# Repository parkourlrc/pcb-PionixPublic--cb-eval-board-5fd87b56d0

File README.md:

# ChargeBridge Evaluation Board

This repository contains the KiCad project files for the **ChargeBridge Evaluation Board**, released as open hardware.

> [!NOTE]  
> KiCad version **9.0.3 or newer** is required to open this project. [Download KiCad](https://www.kicad.org/)

### Overview

This evaluation board is designed to facilitate testing and development with **Pionix ChargeBridge modules**, supporting **all major charging standards**. It is compatible with both **EVSE (Electric Vehicle Supply Equipment)** and **EV (Electric Vehicle)** ChargeBridge modules.

### Use Cases

* **Dual-Board Evaluation Setup**:
  Using two evaluation boards (one with an EVSE module and one with an EV module), you can create a fully functional desktop test environment where the EV module simulates a vehicle being charged by the EVSE module.

* **Standalone Charger Development**:
  A single board can be integrated into a **fully operational AC or DC charger** by connecting appropriate external components such as:

  * Contactors or relays
  * Isolation monitoring devices
  * DC power supplies
  * Power meters

### Mechanical Mounting

The board can be DIN rail mounted using a suitable adapter, enabling integration into control cabinets or industrial test setups.

For more details refer to the PDF datasheet.

## Features

* **Wide Input Voltage Range**:
  `VSUPPLY` input supports **9–30 V**

* **Charging Cable Interface**:
  7-pin connector supporting **all major charging standards**

* **Temperature Sensing**:

  * 2× **PT1000** sensor inputs
  * **On-board PCB temperature monitoring**

* **Relay Control**:

  * 3× relay drivers for **VSUPPLY** (with **feedback** inputs)

* **Output Over Voltage Monitoring**:

  * Input for **DC overvoltage monitoring** (supports up to 1200V)
  * Compliant with **IEC 61851-23:2023**, sections **6.3.1.106.2** and **6.3.1.106.3**

* **Communication Interfaces**:

  * **Ethernet** and **USB-C** for host communication
  * **UART (3.3 V TTL level)**
  * **CAN** with onboard termination
  * **RS485** with onboard termination
  * **Debug UART** pin header compatible with FTDI cables

* **User Interface & Control**:

  * **RGB LED** for charging status indication
  * Push buttons for:

    * Stop charging
    * Emergency stop
    * Module secure
    * Reset
  * **Emergency stop I/O** and **stop charging input** (up to VSUPPLY)

* **General Purpose I/O**:

  * 5× digital inputs
  * 5× digital outputs (all at VSUPPLY level)

* **Power & Measurement**:

  * VSUPPLY voltage monitoring
  * Integrated **shunt resistor** for measuring ChargeBridge current consumption

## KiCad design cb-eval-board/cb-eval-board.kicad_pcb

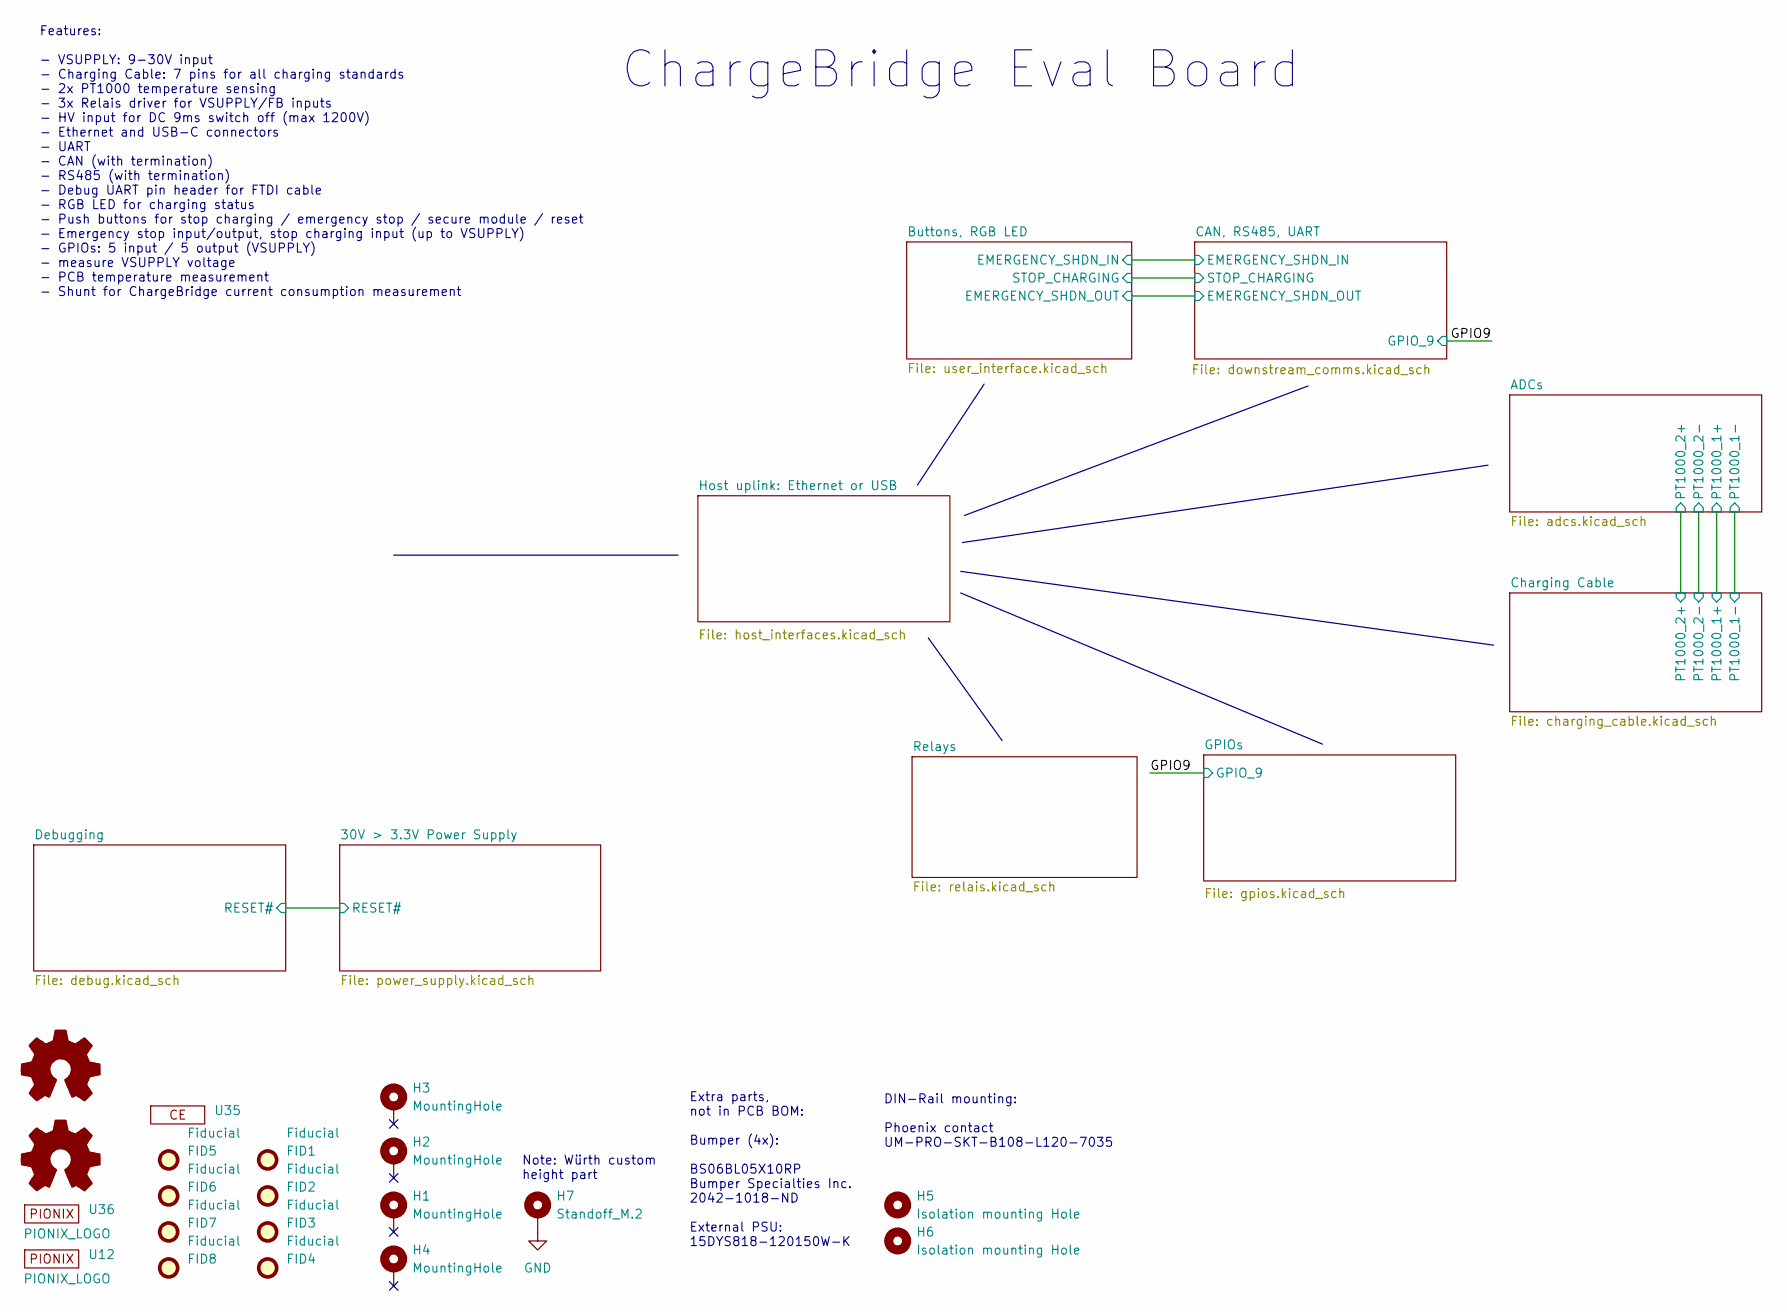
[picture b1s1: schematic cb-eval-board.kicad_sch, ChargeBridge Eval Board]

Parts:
FID1, FID2, FID3, FID4, FID5, FID6, FID7, FID8: Fiducial; Fiducial_0.5mm_Mask1.5mm; MPN DNP
H1, H2, H3, H4: MountingHole; MountingHole_2.2mm_M2_DIN965_Pad; MPN DNP
H5, H6: Isolation mounting Hole; MountingHole_2.7mm_M2.5_ISO14580; MPN DNP
H7: Standoff_M.2; 9774067243R; MPN 9774067243R
SYM1: Logo_Open_Hardware_Small; Symbol_Barrel_Polarity
SYM2: Logo_Open_Hardware_Small; OSHW-Symbol_6.7x6mm_SilkScreen
U12: PIONIX_LOGO; pionix-logo-2_5mm-new; MPN LOGO
U35: CE-Logo_8.5x6mm_SilkScreen
U36: PIONIX_LOGO; pionix-logo-mark; MPN LOGO

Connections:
GND: H7.1; also elsewhere on the board

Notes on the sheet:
Note: Würth custom height part
ChargeBridge Eval Board
DIN-Rail mounting: Phoenix contact UM-PRO-SKT-B108-L120-7035
Extra parts, not in PCB BOM: Bumper (4x): BS06BL05X10RP Bumper Specialties Inc. 2042-1018-ND External PSU: 15DYS818-120150W-K
Features: - VSUPPLY: 9-30V input - Charging Cable: 7 pins for all charging standards - 2x PT1000 temperature sensing - 3x Relais driver for VSUPPLY/FB inputs - HV input for DC 9ms switch off (max 1200V) - Ethernet and USB-C connectors - UART - CAN (with termination) - RS485 (with termination) - Deb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

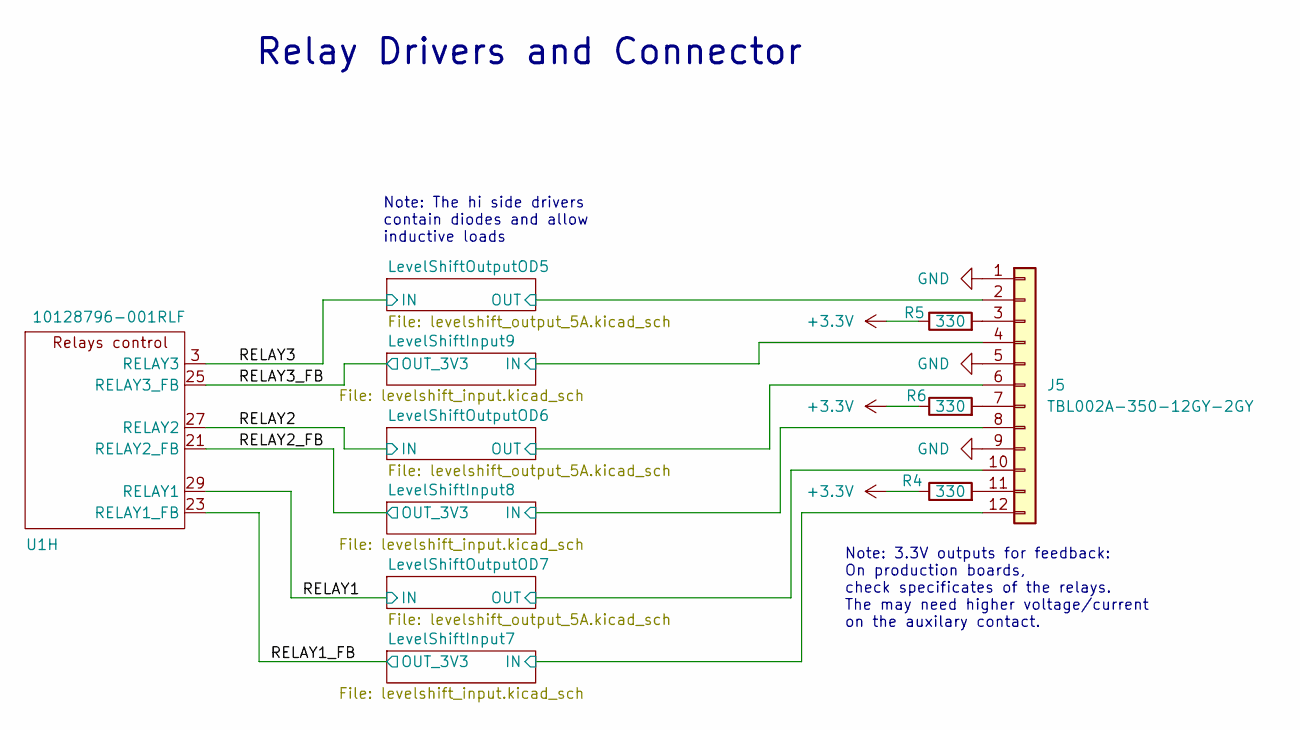
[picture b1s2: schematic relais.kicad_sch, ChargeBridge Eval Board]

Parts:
J5: TBL002A-350-12GY-2GY; CUI_TBL002A-350-12GY-2GY; MPN TBL002A-350-12GY-2GY; Digikey 102-6375-ND
R4, R5, R6: 330; R_0603_1608Metric; MPN RMCF0603FT330R; Digikey RMCF0603FT330RCT-ND
U1: 10128796-001RLF; AMPHENOL_10128796-001RLF_ChargeBridge_Wurth_standoff; MPN 10128796-001RLF

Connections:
+3.3V: R4.1, R5.1, R6.1; also elsewhere on the board
/Relays/LevelShiftInput7/IN: J5.12; also elsewhere on the board
/Relays/LevelShiftInput8/IN: J5.8; also elsewhere on the board
/Relays/LevelShiftInput9/IN: J5.4; also elsewhere on the board
/Relays/LevelShiftOutputOD5/OUT: J5.2; also elsewhere on the board
/Relays/LevelShiftOutputOD6/OUT: J5.6; also elsewhere on the board
/Relays/LevelShiftOutputOD7/OUT: J5.10; also elsewhere on the board
/Relays/RELAY1: U1.29 (RELAY1); also elsewhere on the board
/Relays/RELAY1_FB: U1.23 (RELAY1_FB); also elsewhere on the board
/Relays/RELAY2: U1.27 (RELAY2); also elsewhere on the board
/Relays/RELAY2_FB: U1.21 (RELAY2_FB); also elsewhere on the board
/Relays/RELAY3: U1.3 (RELAY3); also elsewhere on the board
/Relays/RELAY3_FB: U1.25 (RELAY3_FB); also elsewhere on the board
GND: J5.1, J5.5, J5.9; also elsewhere on the board
unnamed: J5.3, R5.2
unnamed: J5.7, R6.2
unnamed: J5.11, R4.2

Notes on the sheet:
Relay Drivers and Connector
Note: 3.3V outputs for feedback: On production boards, check specificates of the relays. The may need higher voltage/current on the auxilary contact.
Note: The hi side drivers contain diodes and allow inductive loads

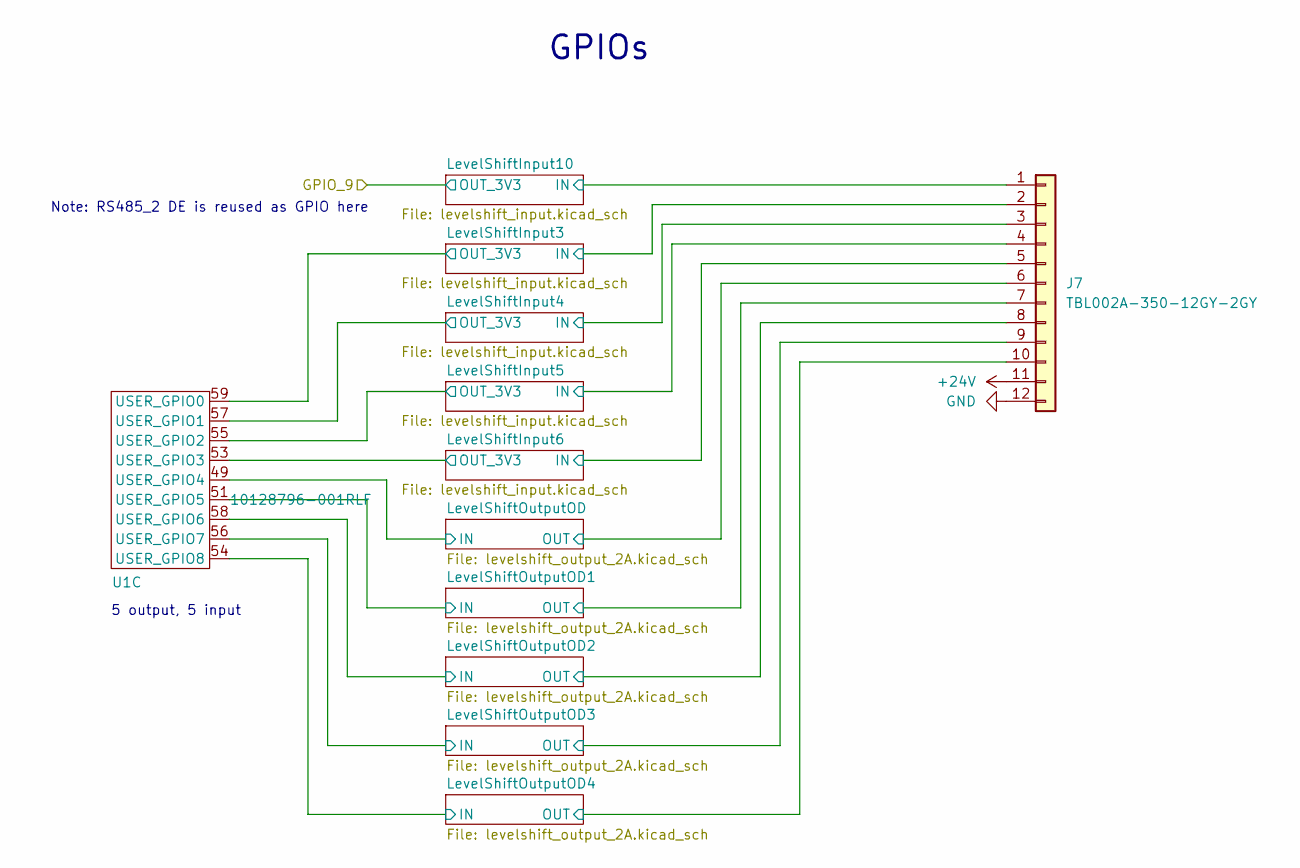
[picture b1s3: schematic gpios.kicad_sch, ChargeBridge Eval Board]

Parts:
J7: TBL002A-350-12GY-2GY; CUI_TBL002A-350-12GY-2GY; MPN TBL002A-350-12GY-2GY; Digikey 102-6375-ND
U1: 10128796-001RLF; AMPHENOL_10128796-001RLF_ChargeBridge_Wurth_standoff; MPN 10128796-001RLF

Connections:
+24V: J7.11; also elsewhere on the board
/GPIOs/LevelShiftInput3/IN: J7.2; also elsewhere on the board
/GPIOs/LevelShiftInput3/OUT_3V3: U1.59 (USER_GPIO0); also elsewhere on the board
/GPIOs/LevelShiftInput4/IN: J7.3; also elsewhere on the board
/GPIOs/LevelShiftInput4/OUT_3V3: U1.57 (USER_GPIO1); also elsewhere on the board
/GPIOs/LevelShiftInput5/IN: J7.4; also elsewhere on the board
/GPIOs/LevelShiftInput5/OUT_3V3: U1.55 (USER_GPIO2); also elsewhere on the board
/GPIOs/LevelShiftInput6/IN: J7.5; also elsewhere on the board
/GPIOs/LevelShiftInput6/OUT_3V3: U1.53 (USER_GPIO3); also elsewhere on the board
/GPIOs/LevelShiftInput10/IN: J7.1; also elsewhere on the board
/GPIOs/LevelShiftOutputOD1/IN: U1.51 (USER_GPIO5); also elsewhere on the board
/GPIOs/LevelShiftOutputOD1/OUT: J7.7; also elsewhere on the board
/GPIOs/LevelShiftOutputOD2/IN: U1.58 (USER_GPIO6); also elsewhere on the board
/GPIOs/LevelShiftOutputOD2/OUT: J7.8; also elsewhere on the board
/GPIOs/LevelShiftOutputOD3/IN: U1.56 (USER_GPIO7); also elsewhere on the board
/GPIOs/LevelShiftOutputOD3/OUT: J7.9; also elsewhere on the board
/GPIOs/LevelShiftOutputOD4/IN: U1.54 (USER_GPIO8); also elsewhere on the board
/GPIOs/LevelShiftOutputOD4/OUT: J7.10; also elsewhere on the board
/GPIOs/LevelShiftOutputOD/IN: U1.49 (USER_GPIO4); also elsewhere on the board
/GPIOs/LevelShiftOutputOD/OUT: J7.6; also elsewhere on the board
GND: J7.12; also elsewhere on the board

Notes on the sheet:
5 output, 5 input
GPIOs
Note: RS485_2 DE is reused as GPIO here

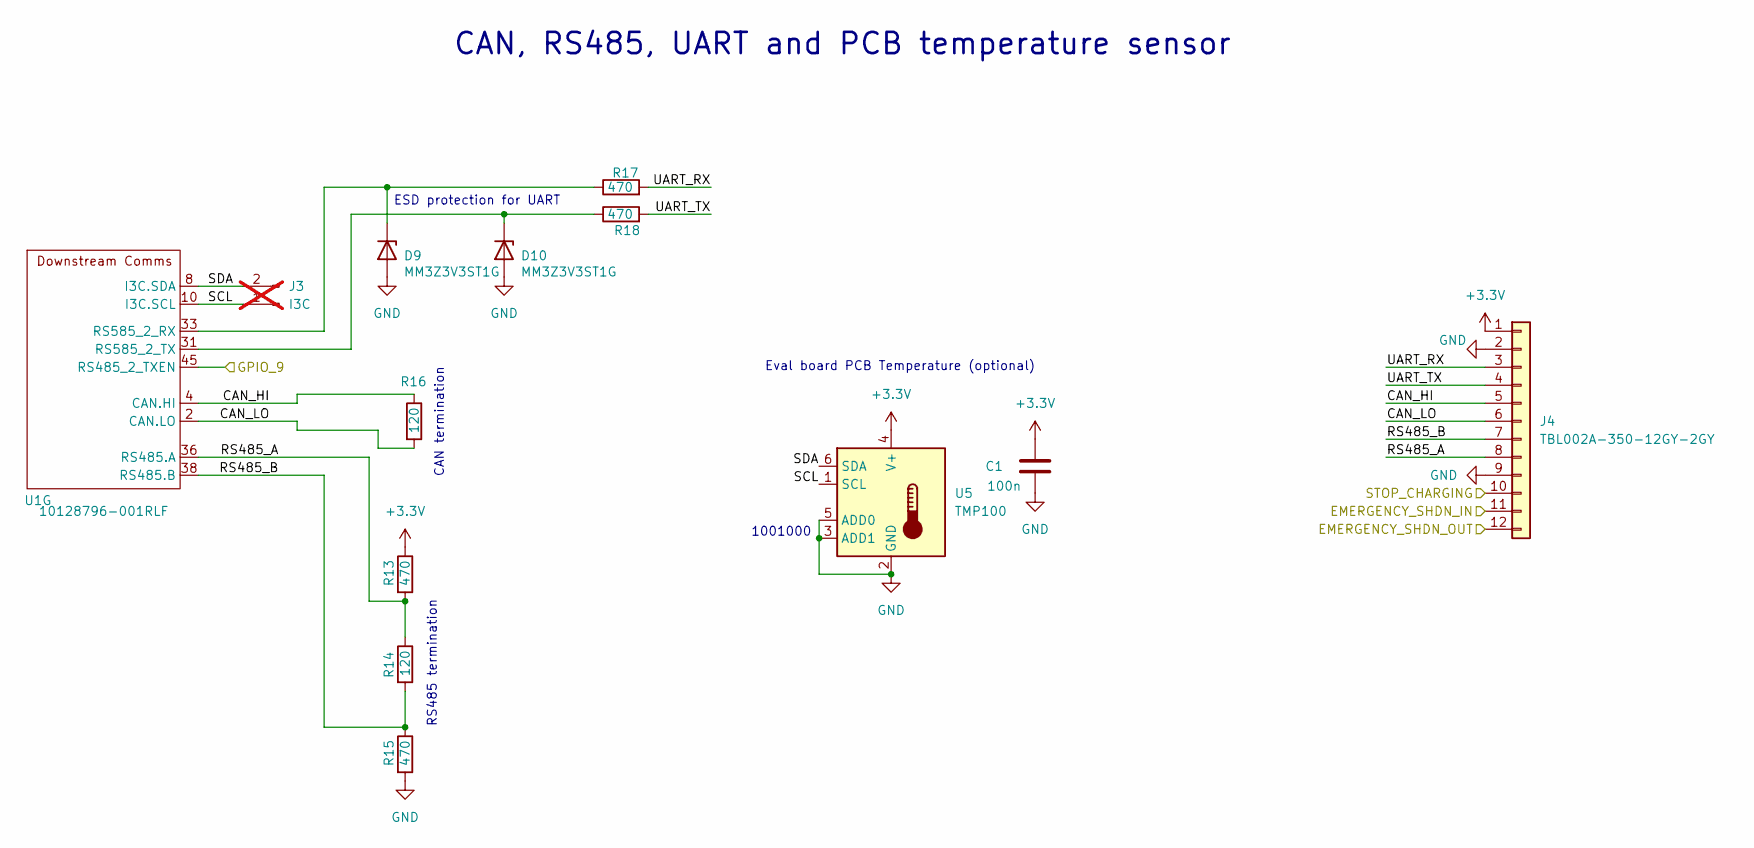
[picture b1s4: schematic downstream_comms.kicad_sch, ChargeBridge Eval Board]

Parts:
C1: 100n; C_0603_1608Metric; MPN C0603C104K5RACAUTO; Digikey 399-6856-1-ND
D9, D10: MM3Z3V3ST1G; D_SOD-323; MPN MM3Z3V3ST1G; Digikey MM3Z3V3ST1GOSCT-ND
J3: I3C; PinHeader_1x02_P2.54mm_Vertical; MPN DNP; not fitted
J4: TBL002A-350-12GY-2GY; CUI_TBL002A-350-12GY-2GY; MPN TBL002A-350-12GY-2GY; Digikey 102-6375-ND
R13, R15, R17, R18: 470; R_0603_1608Metric; MPN RMCF0603FT470R; Digikey RMCF0603FT470RCT-ND
R14, R16: 120; R_0603_1608Metric; MPN RMCF0603FT120R; Digikey RMCF0603FT120RCT-ND
U1: 10128796-001RLF; AMPHENOL_10128796-001RLF_ChargeBridge_Wurth_standoff; MPN 10128796-001RLF
U5: TMP100; SOT-23-6; MPN TMP100NA/3K; Digikey 296-26833-1-ND

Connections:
+3.3V: C1.1, J4.1, R13.1, U5.4 (V+); also elsewhere on the board
/Buttons, RGB LED/EMERGENCY_SHDN_IN: J4.11; also elsewhere on the board
/Buttons, RGB LED/EMERGENCY_SHDN_OUT: J4.12; also elsewhere on the board
/Buttons, RGB LED/STOP_CHARGING: J4.10; also elsewhere on the board
/CAN, RS485, UART/CAN_HI: J4.5, R16.1, U1.4 (CAN.HI)
/CAN, RS485, UART/CAN_LO: J4.6, R16.2, U1.2 (CAN.LO)
/CAN, RS485, UART/RS485_A: J4.8, R13.2, R14.1, U1.36 (RS485.A)
/CAN, RS485, UART/RS485_B: J4.7, R14.2, R15.1, U1.38 (RS485.B)
/CAN, RS485, UART/SCL: J3.1, U1.10 (I3C.SCL), U5.1 (SCL)
/CAN, RS485, UART/SDA: J3.2, U1.8 (I3C.SDA), U5.6 (SDA)
/CAN, RS485, UART/UART_RX: J4.3, R17.2
/CAN, RS485, UART/UART_TX: J4.4, R18.2
/GPIO9: U1.45 (RS485_2_TXEN); also elsewhere on the board
GND: C1.2, D9.2 (A), D10.2 (A), J4.2, J4.9, R15.2, U5.2 (GND), U5.3 (ADD1), U5.5 (ADD0); also elsewhere on the board
unnamed: D9.1 (K), R17.1, U1.33 (RS585_2_RX)
unnamed: D10.1 (K), R18.1, U1.31 (RS585_2_TX)

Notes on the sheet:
Eval board PCB Temperature (optional)
1001000
ESD protection for UART
CAN termination
RS485 termination
CAN, RS485, UART and PCB temperature sensor

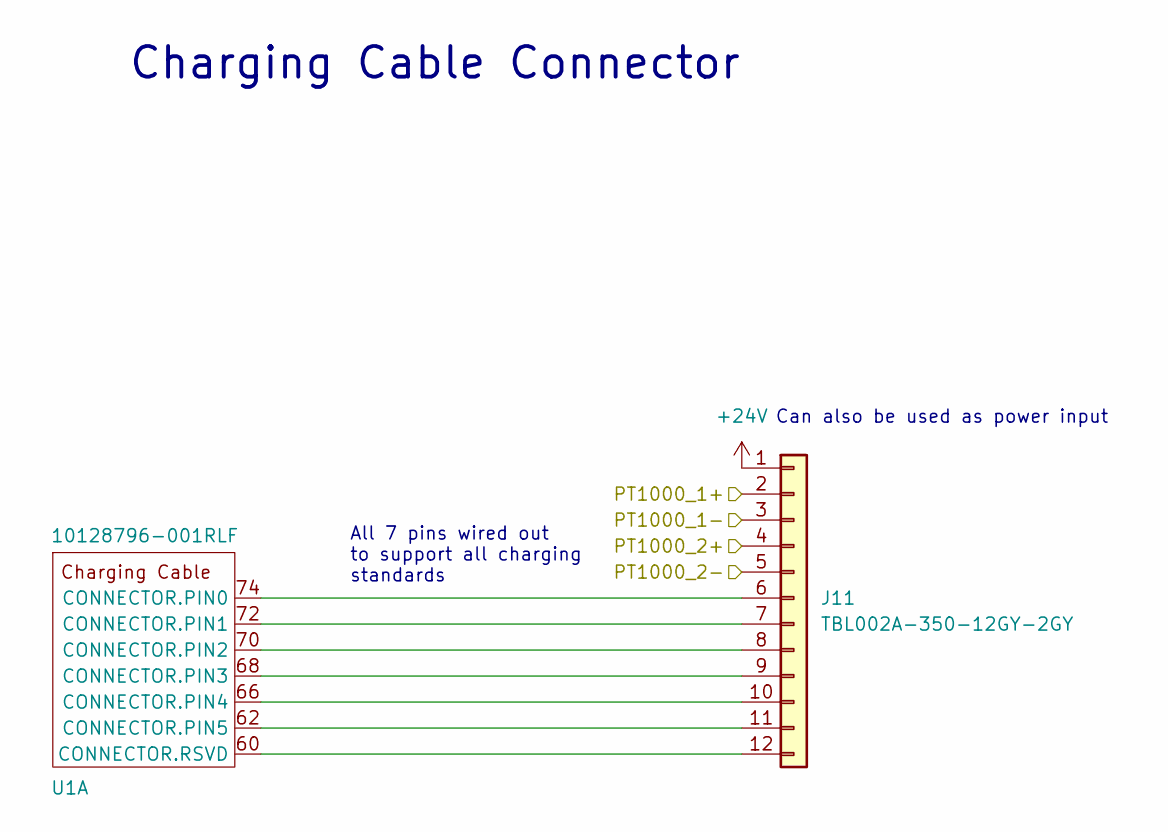
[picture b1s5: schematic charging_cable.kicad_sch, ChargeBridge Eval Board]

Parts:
J11: TBL002A-350-12GY-2GY; CUI_TBL002A-350-12GY-2GY; MPN TBL002A-350-12GY-2GY; Digikey 102-6375-ND
U1: 10128796-001RLF; AMPHENOL_10128796-001RLF_ChargeBridge_Wurth_standoff; MPN 10128796-001RLF

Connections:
+24V: J11.1; also elsewhere on the board
/ADCs/PT1000_1+: J11.2; also elsewhere on the board
/ADCs/PT1000_1-: J11.3; also elsewhere on the board
/ADCs/PT1000_2+: J11.4; also elsewhere on the board
/ADCs/PT1000_2-: J11.5; also elsewhere on the board
unnamed: J11.6, U1.74 (CONNECTOR.PIN0)
unnamed: J11.7, U1.72 (CONNECTOR.PIN1)
unnamed: J11.8, U1.70 (CONNECTOR.PIN2)
unnamed: J11.9, U1.68 (CONNECTOR.PIN3)
unnamed: J11.10, U1.66 (CONNECTOR.PIN4)
unnamed: J11.11, U1.62 (CONNECTOR.PIN5)
unnamed: J11.12, U1.60 (CONNECTOR.RSVD)

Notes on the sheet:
Charging Cable Connector
Can also be used as power input
All 7 pins wired out to support all charging standards

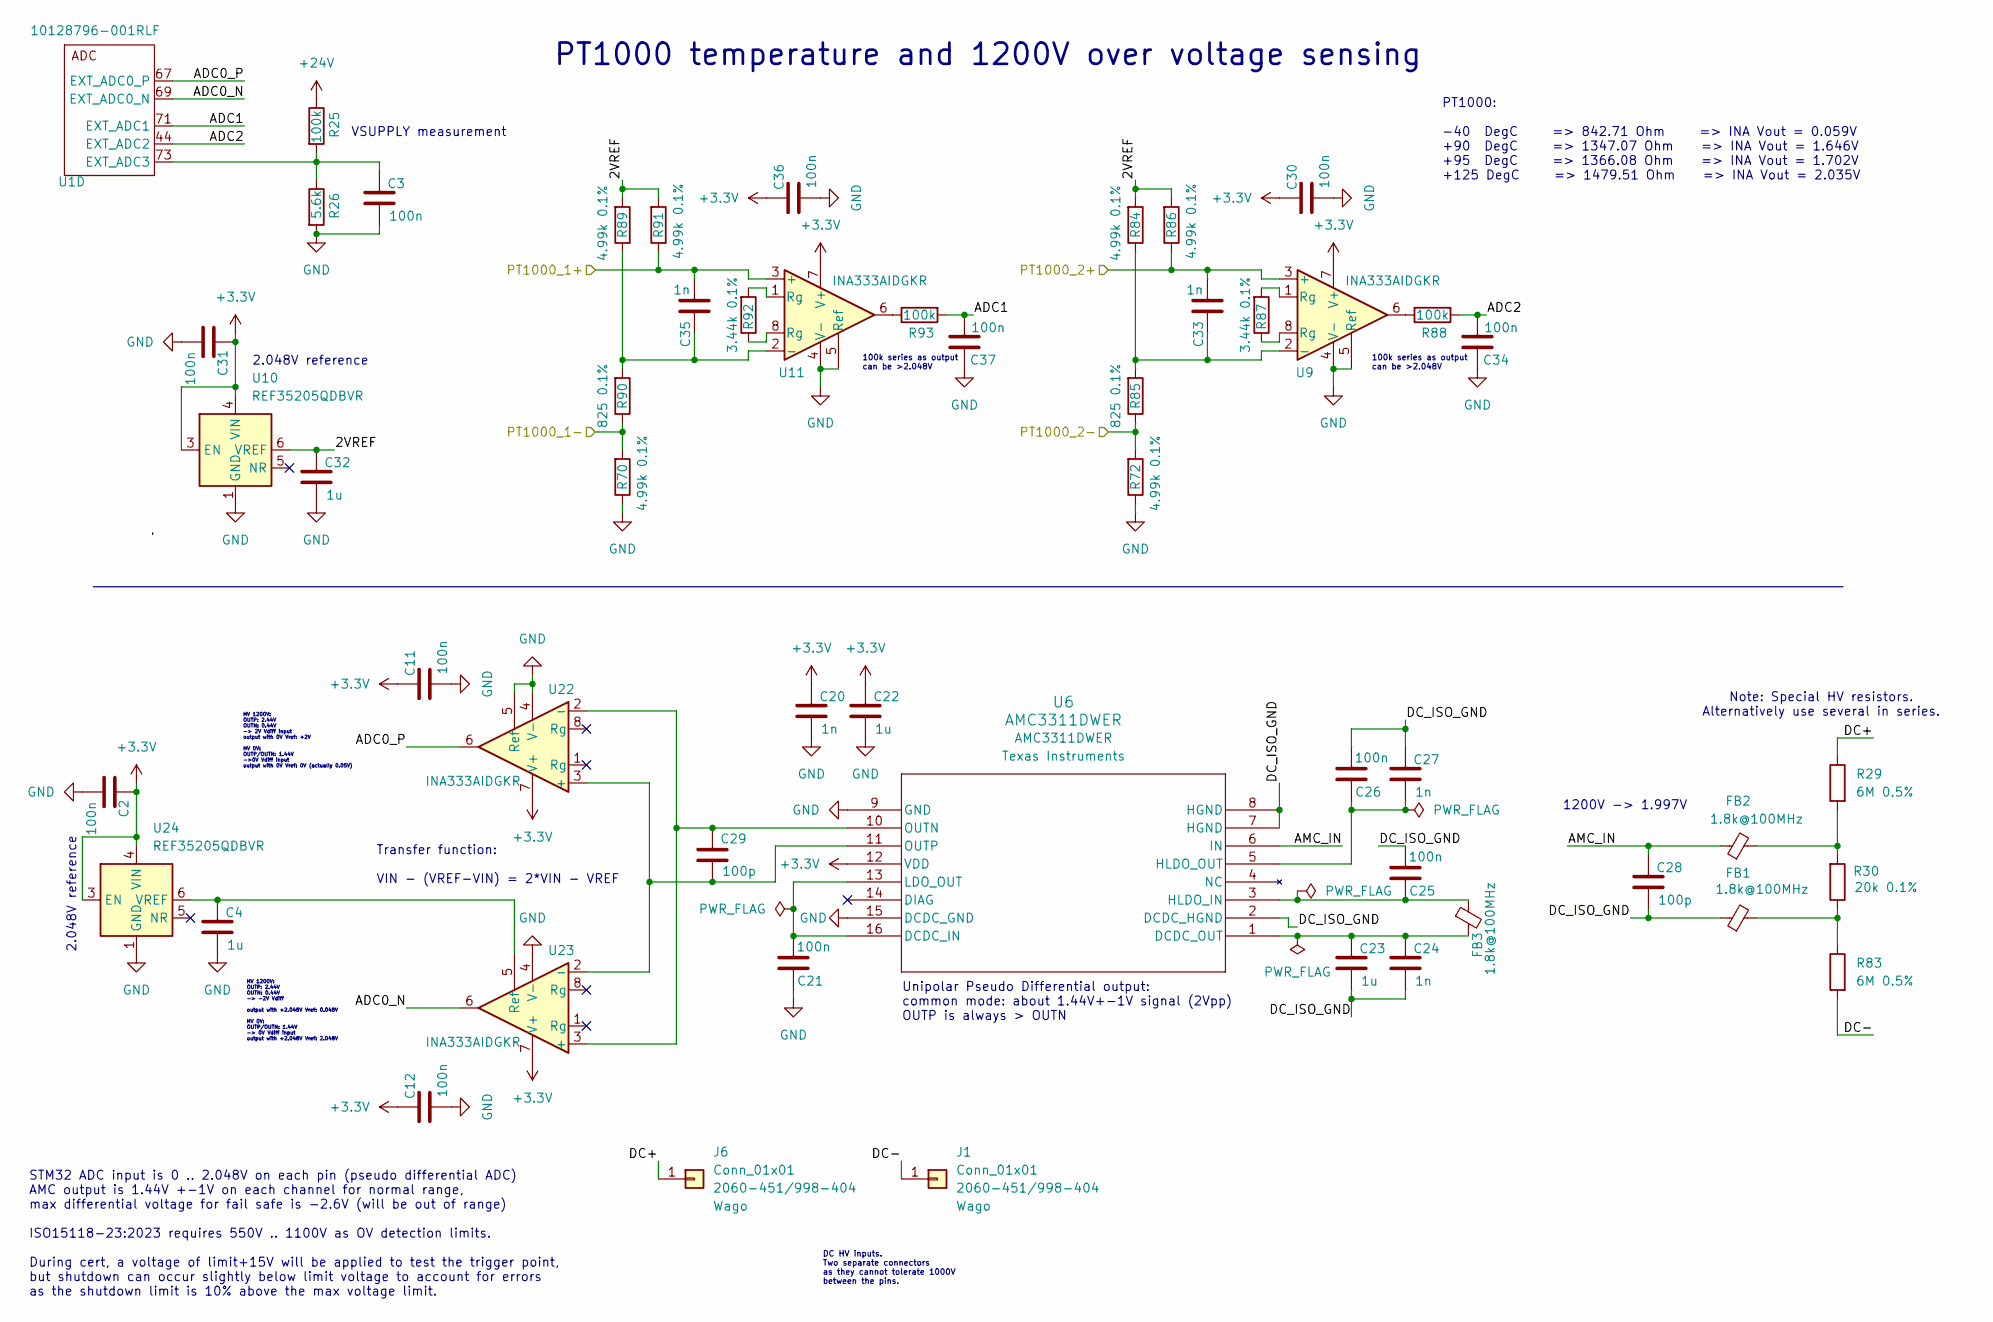
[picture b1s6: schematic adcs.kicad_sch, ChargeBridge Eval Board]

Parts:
C2, C3, C11, C12, C21, C25, C26, C30, C31, C34, C36, C37: 100n; C_0603_1608Metric; MPN C0603C104K5RACAUTO; Digikey 399-6856-1-ND
C4, C22, C23, C32: 1u; C_0603_1608Metric; MPN C0603C105K3PACTU; Digikey 399-C0603C105K3PACTUCT-ND
C20, C24, C27, C33, C35: 1n; C_0603_1608Metric; MPN C0603C102K5RACTU; Digikey 399-C0603C102K5RACTUCT-ND
C28, C29: 100p; C_0603_1608Metric; MPN 0603N101J500CT; Digikey 1292-1644-1-ND
FB1, FB2, FB3: 1.8k@100MHz; L_0603_1608Metric; MPN 742792692; Digikey 732-4671-1-ND
J1, J6: Conn_01x01; 2060451998404; MPN 2060-451/998-404; Digikey 2946-2060-451/998-404CT-ND
R25, R88, R93: 100k; R_0603_1608Metric; MPN RMCF0603FT100K; Digikey RMCF0603FT100KCT-ND
R26: 5.6k; R_0603_1608Metric; MPN RMCF0603FT5K60; Digikey RMCF0603FT5K60CT-ND
R29, R83: 6M 0.5%; R_1206_3216Metric; MPN CRMA1206AF6M00DKEF; JLCPCB Part# C3986300
R30: 20k 0.1%; R_0603_1608Metric; MPN ERA-3AEB203V; JLCPCB Part# C469660
R70, R72, R84, R86, R89, R91: 4.99k 0.1%; R_0603_1608Metric; MPN ERA-3AEB4991V; Digikey P4.99KDBCT-ND
R85, R90: 825 0.1%; R_0603_1608Metric; MPN ERA-3AEB8250V; Digikey P909DBCT-ND
R87, R92: 3.44k 0.1%; R_0603_1608Metric; MPN RN73R1JTTD3441B25; Digikey P8.2KDBCT-ND
U1: 10128796-001RLF; AMPHENOL_10128796-001RLF_ChargeBridge_Wurth_standoff; MPN 10128796-001RLF
U6: AMC3311DWER; SOIC16_7P5X10P3_TEX; MPN AMC3311DWER; Digikey 296-AMC3311DWERCT-ND
U9, U11, U22, U23: INA333AIDGKR; VSSOP-8_3x3mm_P0.65mm; MPN INA333AIDGKR; Digikey 296-23564-1-ND
U10, U24: REF35205QDBVR; SOT-23-6; MPN REF35205QDBVR; Digikey 296-REF35205QDBVRCT-ND

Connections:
+3.3V: C2.1, C11.1, C12.1, C20.1, C22.1, C30.1, C31.1, C36.1, U6.12 (VDD), U9.7 (V+), U10.3 (EN), U10.4 (VIN), U11.7 (V+), U22.7 (V+), U23.7 (V+), U24.3 (EN), U24.4 (VIN); also elsewhere on the board
+24V: R25.1; also elsewhere on the board
/ADCs/2VREF: C32.1, R84.2, R86.2, R89.2, R91.2, U10.6 (VREF)
/ADCs/ADC0_N: U1.69 (EXT_ADC0_N), U23.6
/ADCs/ADC0_P: U1.67 (EXT_ADC0_P), U22.6
/ADCs/ADC1: C37.2, R93.2, U1.71 (EXT_ADC1)
/ADCs/ADC2: C34.2, R88.2, U1.44 (EXT_ADC2)
/ADCs/AMC_IN: C28.1, FB2.1, U6.6 (IN)
/ADCs/DC+: J6.1, R29.1
/ADCs/DC-: J1.1, R83.2
/ADCs/DC_ISO_GND: C23.2, C24.2, C25.2, C26.2, C27.1, C28.2, FB1.1, U6.2 (DCDC_HGND), U6.7 (HGND), U6.8 (HGND)
/ADCs/PT1000_1+: C35.2, R91.1, U11.3 (+); also elsewhere on the board
/ADCs/PT1000_1-: R70.2, R90.1; also elsewhere on the board
/ADCs/PT1000_2+: C33.2, R86.1, U9.3 (+); also elsewhere on the board
/ADCs/PT1000_2-: R72.2, R85.1; also elsewhere on the board
GND: C2.2, C3.2, C4.2, C11.2, C12.2, C20.2, C21.1, C22.2, C30.2, C31.2, C32.2, C34.1, C36.2, C37.1, R26.2, R70.1, R72.1, U6.9 (GND), U6.15 (DCDC_GND), U9.4 (V-), U9.5 (Ref), U10.1 (GND), U10.2 (GND), U11.4 (V-), U11.5 (Ref), U22.4 (V-), U22.5 (Ref), U23.4 (V-), U24.1 (GND), U24.2 (GND); also elsewhere on the board
unnamed: FB1.2, R30.1, R83.1
unnamed: FB2.2, R29.2, R30.2
unnamed: R87.1, U9.8 (Rg)
unnamed: R87.2, U9.1 (Rg)
unnamed: R88.1, U9.6
unnamed: R92.1, U11.8 (Rg)
unnamed: R92.2, U11.1 (Rg)
unnamed: R93.1, U11.6
unnamed: C3.1, R25.2, R26.1, U1.73 (EXT_ADC3)
unnamed: C21.2, U6.13 (LDO_OUT), U6.16 (DCDC_IN)
unnamed: C23.1, C24.1, FB3.2, U6.1 (DCDC_OUT)
unnamed: C25.1, FB3.1, U6.3 (HLDO_IN)
unnamed: C26.1, C27.2, U6.5 (HLDO_OUT)
unnamed: C33.1, R84.1, R85.2, U9.2 (-)
unnamed: C35.1, R89.1, R90.2, U11.2 (-)
unnamed: C29.2, U6.11 (OUTP), U22.3 (+), U23.2 (-)
unnamed: C29.1, U6.10 (OUTN), U22.2 (-), U23.3 (+)
unnamed: C4.1, U23.5 (Ref), U24.6 (VREF)

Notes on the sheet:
HV 1200V: OUTP: 2.44V OUTN: 0.44V -> 2V Vdiff input output with 0V Vref: +2V HV 0V: OUTP/OUTN: 1.44V ->0V Vdiff input output with 0V Vref: 0V (actually 0.05V)
STM32 ADC input is 0 .. 2.048V on each pin (pseudo differential ADC) AMC output is 1.44V +-1V on each channel for normal range, max differential voltage for fail safe is -2.6V (will be out of range) ISO15118-23:2023 requires 550V .. 1100V as OV detection limits. During cert, a voltage of limit+15V 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
100k series as output can be >2.048V
2.048V reference
Transfer function: VIN - (VREF-VIN) = 2*VIN - VREF
DC HV inputs. Two separate connectors as they cannot tolerate 1000V between the pins.
1200V -> 1.997V
HV 1200V: OUTP: 2.44V OUTN: 0.44V -> -2V Vdiff output with +2.048V Vref: 0.048V HV 0V: OUTP/OUTN: 1.44V -> 0V Vdiff input output with +2.048V Vref: 2.048V
Note: Special HV resistors. Alternatively use several in series.
VSUPPLY measurement
PT1000 temperature and 1200V over voltage sensing
PT1000: -40 DegC => 842.71 Ohm => INA Vout = 0.059V +90 DegC => 1347.07 Ohm => INA Vout = 1.646V +95 DegC => 1366.08 Ohm => INA Vout = 1.702V +125 DegC => 1479.51 Ohm => INA Vout = 2.035V
Unipolar Pseudo Differential output: common mode: about 1.44V+-1V signal (2Vpp) OUTP is always > OUTN

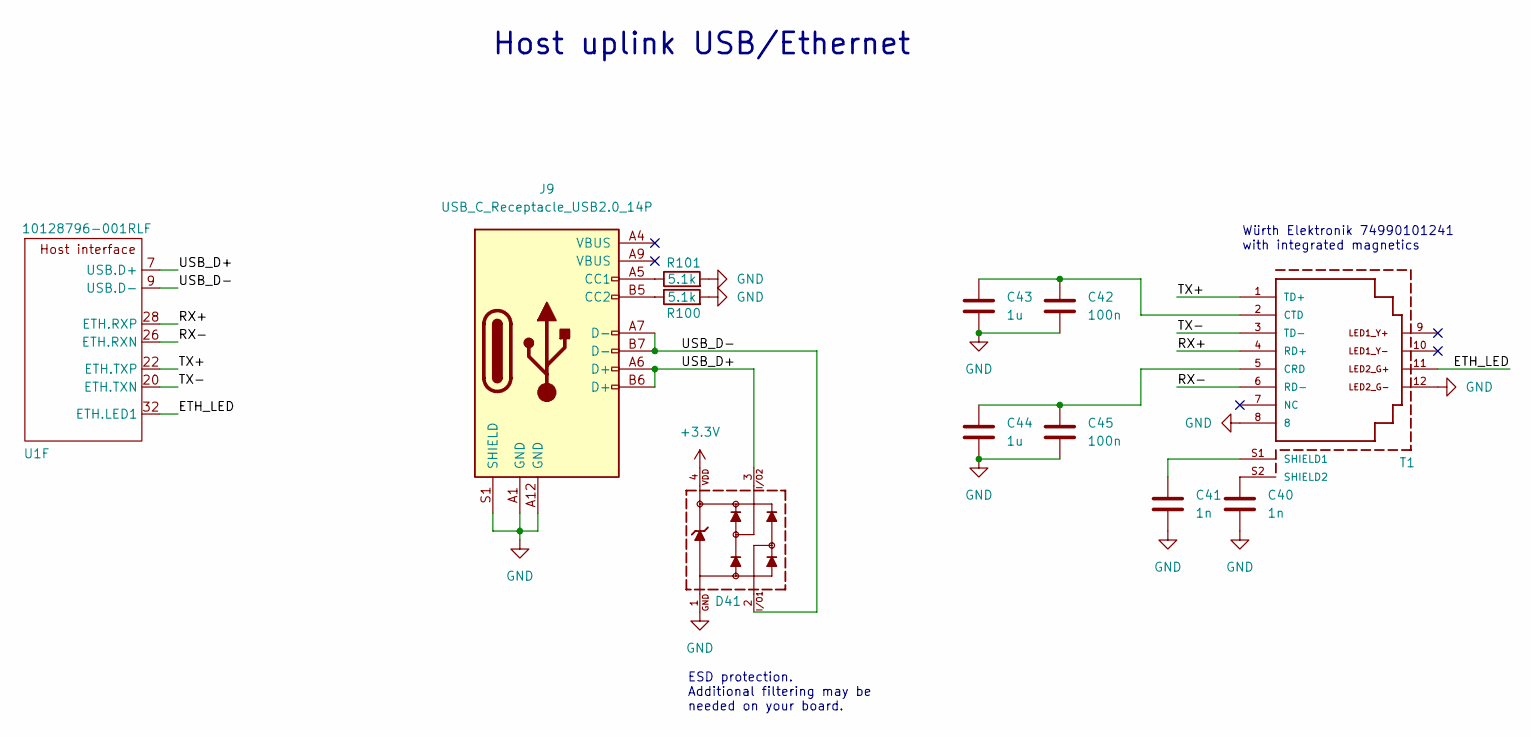
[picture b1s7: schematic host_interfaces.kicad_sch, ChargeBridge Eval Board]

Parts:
C40, C41: 1n; C_0603_1608Metric; MPN C0603C102K5RACTU; Digikey 399-C0603C102K5RACTUCT-ND
C42, C45: 100n; C_0603_1608Metric; MPN C0603C104K5RACAUTO; Digikey 399-6856-1-ND
C43, C44: 1u; C_0603_1608Metric; MPN C0603C105K3PACTU; Digikey 399-C0603C105K3PACTUCT-ND
D41: 5Vdc; WE-TVS_SOT143-4L; MPN STS142050UL08; Digikey 283-STS142050UL08CT-ND
J9: USB_C_Receptacle_USB2.0_14P; USB_C_Receptacle_GCT_USB4110; MPN USB4110-GF-A; Digikey 2073-USB4110-GF-A-1-ND
R100, R101: 5.1k; R_0603_1608Metric; MPN RMCF0603FT5K10; Digikey RMCF0603FT5K10CT-ND
T1: 74990101241; MPN 74990101241; Digikey 732-10834-ND
U1: 10128796-001RLF; AMPHENOL_10128796-001RLF_ChargeBridge_Wurth_standoff; MPN 10128796-001RLF

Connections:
+3.3V: D41.4; also elsewhere on the board
/Host uplink: Ethernet or USB/ETH_LED: T1.11, U1.32 (ETH.LED1)
/Host uplink: Ethernet or USB/RX+: T1.4 (RD+), U1.28 (ETH.RXP)
/Host uplink: Ethernet or USB/RX-: T1.6 (RD-), U1.26 (ETH.RXN)
/Host uplink: Ethernet or USB/TX+: T1.1 (TD+), U1.22 (ETH.TXP)
/Host uplink: Ethernet or USB/TX-: T1.3 (TD-), U1.20 (ETH.TXN)
/Host uplink: Ethernet or USB/USB_D+: D41.3, J9.A6 (D+), J9.B6 (D+), U1.7 (USB.D+)
/Host uplink: Ethernet or USB/USB_D-: D41.2, J9.A7 (D-), J9.B7 (D-), U1.9 (USB.D-)
GND: C40.2, C41.2, C42.2, C43.2, C44.2, C45.2, D41.1, J9.A1 (GND), J9.A12 (GND), J9.S1 (SHIELD), R100.2, R101.2, T1.8, T1.12; also elsewhere on the board
unnamed: J9.A5 (CC1), R101.1
unnamed: J9.B5 (CC2), R100.1
unnamed: C44.1, C45.1, T1.5 (CRD)
unnamed: C42.1, C43.1, T1.2 (CTD)
unnamed: C41.1, T1.S1 (SHIELD1)
unnamed: C40.1, T1.S2 (SHIELD2)

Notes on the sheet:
Würth Elektronik 74990101241 with integrated magnetics
Host uplink USB/Ethernet
ESD protection. Additional filtering may be needed on your board.

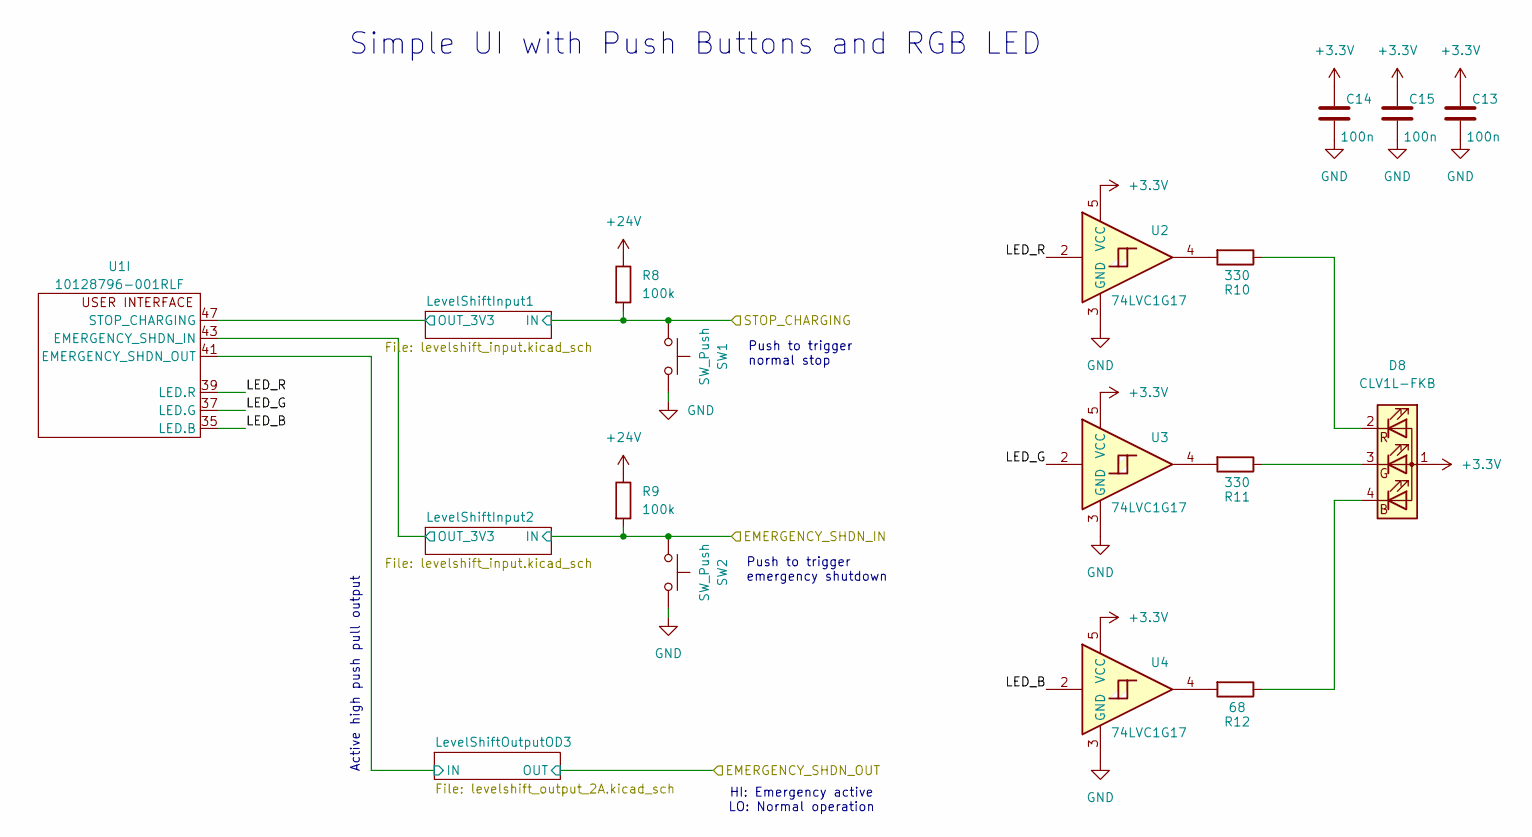
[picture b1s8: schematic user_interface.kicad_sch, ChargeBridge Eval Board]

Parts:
C13, C14, C15: 100n; C_0603_1608Metric; MPN C0603C104K5RACAUTO; Digikey 399-6856-1-ND
D8: CLV1L-FKB; LED_Cree-PLCC4_3.2x2.8mm_CCW; MPN CLV1L-FKB-CJQRNQEFGBB79353; Digikey 90-CLV1L-FKB-CJQRNQEFGBB79353CT-ND
R8, R9: 100k; R_0603_1608Metric; MPN RMCF0603FT100K; Digikey RMCF0603FT100KCT-ND
R10, R11: 330; R_0603_1608Metric; MPN RMCF0603FT330R; Digikey RMCF0603FT330RCT-ND
R12: 68; R_0603_1608Metric; MPN RMCF0603FT68R0; Digikey RMCF0603FT68R0CT-ND
SW1, SW2: SW_Push; SW_TS02-66-70-BK-160-LCR-D; MPN TS02-66-70-BK-160-LCR-D; Digikey 2223-TS02-66-70-BK-160-LCR-D-ND
U1: 10128796-001RLF; AMPHENOL_10128796-001RLF_ChargeBridge_Wurth_standoff; MPN 10128796-001RLF
U2, U3, U4: 74LVC1G17; SOT-353_SC-70-5; MPN SN74LVC1G17DCKR; Digikey 296-11934-1-ND

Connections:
+3.3V: C13.1, C14.1, C15.1, D8.1 (A), U2.5 (VCC), U3.5 (VCC), U4.5 (VCC); also elsewhere on the board
+24V: R8.1, R9.1; also elsewhere on the board
/Buttons, RGB LED/EMERGENCY_SHDN_IN: R9.2, SW2.1; also elsewhere on the board
/Buttons, RGB LED/LED_B: U1.35 (LED.B), U4.2
/Buttons, RGB LED/LED_G: U1.37 (LED.G), U3.2
/Buttons, RGB LED/LED_R: U1.39 (LED.R), U2.2
/Buttons, RGB LED/LevelShiftInput1/OUT_3V3: U1.47 (STOP_CHARGING); also elsewhere on the board
/Buttons, RGB LED/LevelShiftInput2/OUT_3V3: U1.43 (EMERGENCY_SHDN_IN); also elsewhere on the board
/Buttons, RGB LED/LevelShiftOutputOD3/IN: U1.41 (EMERGENCY_SHDN_OUT); also elsewhere on the board
/Buttons, RGB LED/STOP_CHARGING: R8.2, SW1.1; also elsewhere on the board
GND: C13.2, C14.2, C15.2, SW1.2, SW2.2, U2.3 (GND), U3.3 (GND), U4.3 (GND); also elsewhere on the board
unnamed: D8.4 (BK), R12.1
unnamed: D8.3 (GK), R11.1
unnamed: D8.2 (RK), R10.1
unnamed: R10.2, U2.4
unnamed: R11.2, U3.4
unnamed: R12.2, U4.4

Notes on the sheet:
Active high push pull output
HI: Emergency active LO: Normal operation
Simple UI with Push Buttons and RGB LED
Push to trigger emergency shutdown
Push to trigger normal stop

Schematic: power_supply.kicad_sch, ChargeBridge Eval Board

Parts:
C5, C6: 4.7u 50V; C_1210_3225Metric; MPN C3225X7R1H475K250AB; Digikey 445-7726-1-ND
C7: 1u; C_0603_1608Metric; MPN C0603C105K3PACTU; Digikey 399-C0603C105K3PACTUCT-ND
C8: 10u; C_0603_1608Metric; MPN GRM188R6YA106MA73J; Digikey 490-GRM188R6YA106MA73JCT-ND
C9: 100n; C_0603_1608Metric; MPN C0603C104K5RACAUTO; Digikey 399-6856-1-ND
C10: 100u 6.3V; C_1206_3216Metric; MPN JMK316ABJ107ML-T; Digikey 587-3395-1-ND
J10: Barrel_Jack_Switch; CUI_PJ-044AH; MPN PJ-044AH; Digikey CP-044AH-ND
R32: 10k; R_0603_1608Metric; MPN RMCF0603FT10K0; Digikey RMCF0603FT10K0CT-ND
R33: 5.6k; R_0603_1608Metric; MPN RMCF0603FT5K60; Digikey RMCF0603FT5K60CT-ND
R34: 402k; R_0603_1608Metric; MPN RMCF0603FT402K
R35: 137k; R_0603_1608Metric; MPN RMCF0603FT137k
R63: 50m; R_1206_3216Metric; MPN CSR1206FT50L0; Digikey CSR1206FT50L0CT-ND
R120: 0; R_0603_1608Metric; MPN RMCF0603ZT0R00; Digikey RMCF0603ZT0R00CT-ND
U1: 10128796-001RLF; AMPHENOL_10128796-001RLF_ChargeBridge_Wurth_standoff; MPN 10128796-001RLF
U37: 171023801; WPME-VDLM_LGA-12EP; MPN 171023801; Digikey 732-171023801CT-ND

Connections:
+3.3V: C9.1, C10.1, R32.1, R34.1, R63.1, U37.6 (VOUT), U37.7 (VOUT); also elsewhere on the board
+24V: C5.1, C6.1, J10.1, U37.4 (VIN), U37.5 (VIN); also elsewhere on the board
/30V > 3.3V Power Supply/CB_VCC: C8.2, R63.2, U1.11 (VDD3v3), U1.40 (VDD3v3), U1.46 (VDD3v3), U1.48 (VDD3v3), U1.61 (VDD3v3)
/30V > 3.3V Power Supply/RESET#: R32.2, R120.1; also elsewhere on the board
GND: C5.2, C6.2, C7.2, C8.1, C9.2, C10.2, J10.2, R35.2, U1.6 (GND), U1.24 (GND), U1.34 (GND), U1.50 (GND), U1.52 (GND), U1.64 (GND), U1.75 (GND), U1.SH1, U1.SH2, U37.10 (AGND), U37.EP (PGND); also elsewhere on the board
unnamed: U37.9 (VIN_INT_CONN), U37.12 (ENABLE)
unnamed: R34.2, R35.1, U37.2 (FB)
unnamed: R33.1, U37.1 (FSW)
unnamed: R120.2, U37.11 (PG)
unnamed: C7.1, R33.2, U37.3 (VCC)

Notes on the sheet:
5V - 36V input, 3.3V output
Shunt to measure CB current consumption. Do not use shunt on production boards, connect power pins directly to power rail and decouple at each pin.
ChargeBridge power connection
External power input
700kHz

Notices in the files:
cb-eval-board/adcs.kicad_sch:
License: CERN-OHL-P
